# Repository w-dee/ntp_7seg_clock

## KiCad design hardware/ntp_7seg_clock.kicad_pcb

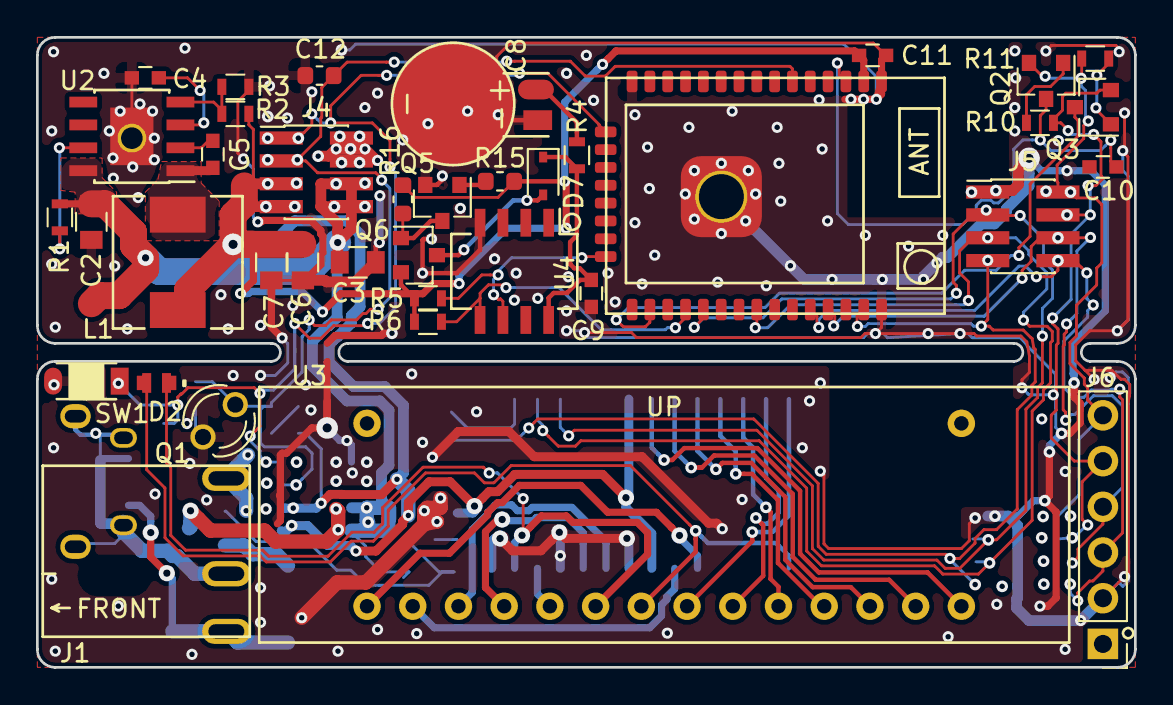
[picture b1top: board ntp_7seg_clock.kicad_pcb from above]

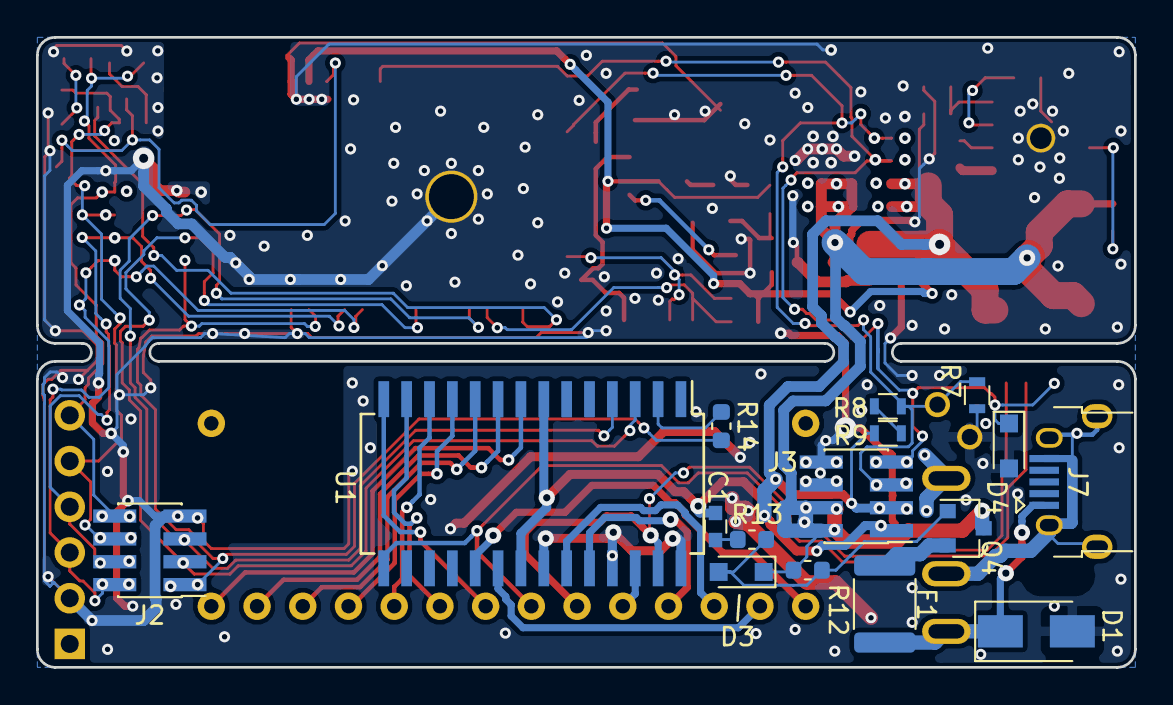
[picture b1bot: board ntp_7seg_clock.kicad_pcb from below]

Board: 2 copper layers, 61.0 x 35.0 mm, 54 parts (16 on the bottom side), 48 nets.

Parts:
C1, C5, C9, C10: 0.1u; C_0603
C2, C3, C6, C7: 10u/35V; C_0805
C4: 2.2u; C_0603
C8: ML621; BAT_MS621T_LAY
C11: 1u; C_0603
C12: 2.2u; C_0603_1608Metric
D1: 28V TVS; D_SMA
D2: LED; LED1608_Handsoldering
D3, D4: ESD5Z3.3T1G; D_SOD-323_HandSoldering
D7: SBD; D_SOD-323
F1: 1A hold; Fuse_1812_4532Metric
J1: Barrel_Jack; DC-044
J2, J3, J4, J5: Conn_02x04_Odd_Even; Pin_Header_Straight_2x04_Pitch1.27mm_SMD
J6: Conn_01x06_Male; Pin_Header_Straight_1x06_Pitch2.54mm
J7: USB_B_Micro; USB_Micro-B_Jing_A01SB141B1-067
L1: 10uH; Inductor_Wurth_HCM-7050
Q1: NJL7302L-F3; LED_D3.0mm
Q2, Q3, Q5: Q_NPN_BEC; SOT-23
Q4, Q6: AO3401; SOT-23
R1: 100k; R_0603
R2: 49.9k; R_0603
R3: 16k; R_0603
R4: 1k; R_0603
R5, R6: 4.7k; R_0603
R7, R8, R10, R11: 10k; R_0603
R9: 22k; R_0603
R12: 1M; R_0603_1608Metric
R13: 22K; R_0603_1608Metric
R14: 120R; R_0603_1608Metric
R15, R16: 10k; R_0603_1608Metric
SW1: SW_PUSH_SMALL_H; TACT_SW_SMD_Panasonic-EVPAWBD2A
U1: TM1627; SOIC-28W_7.5x18.7mm_Pitch1.27mm
U2: JW5150A; HTSOP-8-1EP_3.9x4.9mm_Pitch1.27mm
U3: 6digit_7segment_led_for_clock_3662B; LED_MODULE-CLOCK-3662B
U4: PCF8563; SOIC-8_3.9x7.0mm_Pitch1.27mm
U5: TTGO-Micro32-Ver2; TTGO-Micro32

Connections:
+3V3: C1.1, C6.1, C7.1, C11.1, J3.1, J3.3, J4.5, J4.7, L1.2, Q6.2, R2.2, R5.2, R6.2, R9.2, R15.1, R16.1, U1.7, U1.21, U5.2
/3V3_RTC: C9.1, D7.1, R4.2, U4.8
/VIN: C2.1, C3.1, D3.1, J3.2, J3.4, J4.6, J4.8, Q4.3, R1.1, R12.2, U2.8
DTR: J2.6, J5.4, J6.5, Q3.2, R10.2
E_AIN: C12.1, J3.5, J4.3, Q1.2, R7.2, R8.1, U5.6
E_BUTTON: D4.1, J3.7, J4.1, SW1.2, U5.16
E_EN: C10.2, Q2.3, U5.3
E_GPIO0: Q3.3, U5.25
E_LED_CLK: J2.3, J5.5, U1.3, U5.31
E_LED_DIO: J2.1, J5.7, R14.2, U5.37
E_LED_STB: J2.5, J5.3, U1.4, U5.28
E_RX: J2.2, J5.8, J6.3, U5.34
E_SCL: R5.1, U4.6, U5.23
E_SDA: R6.1, U4.5, U5.27
E_TX: J2.4, J5.6, J6.4, U5.35
GND: C1.2, C2.2, C3.2, C4.2, C6.2, C7.2, C8.2, C9.2, C10.1, C11.2, C12.2, D1.2, D4.2, J1.2, J2.7, J3.6, J3.8, J4.2, J4.4, J5.1, J6.2, Q1.1, Q5.2, R3.1, R7.1, R13.1, SW1.1, U1.22, U1.25, U1.28, U2.9, U4.4, U5.1, U5.15, U5.38, U5.39
unnamed: C4.1, U2.3
unnamed: C5.1, U2.2
unnamed: C5.2, L1.1, U2.1
unnamed: C8.1, R4.1
unnamed: D1.1, F1.1, J1.1, J7.1
unnamed: D2.1, U1.27, U3.6
unnamed: D2.2, U1.15, U3.7
unnamed: D3.2, Q4.1, R12.1, R13.2
unnamed: D7.2, Q6.3
unnamed: F1.2, Q4.2
unnamed: J1.3, J7.5, J7.6
unnamed: Q2.1, R10.1
unnamed: Q3.1, R11.1
unnamed: Q5.1, R15.2
unnamed: Q5.3, Q6.1, R16.2
unnamed: R1.2, U2.7
unnamed: R2.1, R3.2, U2.4
unnamed: R8.2, R9.1
unnamed: R14.1, U1.2
unnamed: U1.8, U3.14
unnamed: U1.9, U3.13
unnamed: U1.10, U3.12
unnamed: U1.11, U3.11
unnamed: U1.12, U3.10
unnamed: U1.13, U3.9
unnamed: U1.14, U3.8
unnamed: U1.19, U3.1
unnamed: U1.20, U3.2
unnamed: U1.23, U3.3
unnamed: U1.24, U3.4
unnamed: U1.26, U3.5
RTS: J2.8, J5.2, J6.6, Q2.2, R11.2

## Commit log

2018-11-12 Improved RTC 3V3 backup voltage handling
2018-11-12 Ooops reverse protection FET is reversed; and others
2018-11-14 Modified to use Li-ion rechargable battery
2018-11-22 Layout fix
